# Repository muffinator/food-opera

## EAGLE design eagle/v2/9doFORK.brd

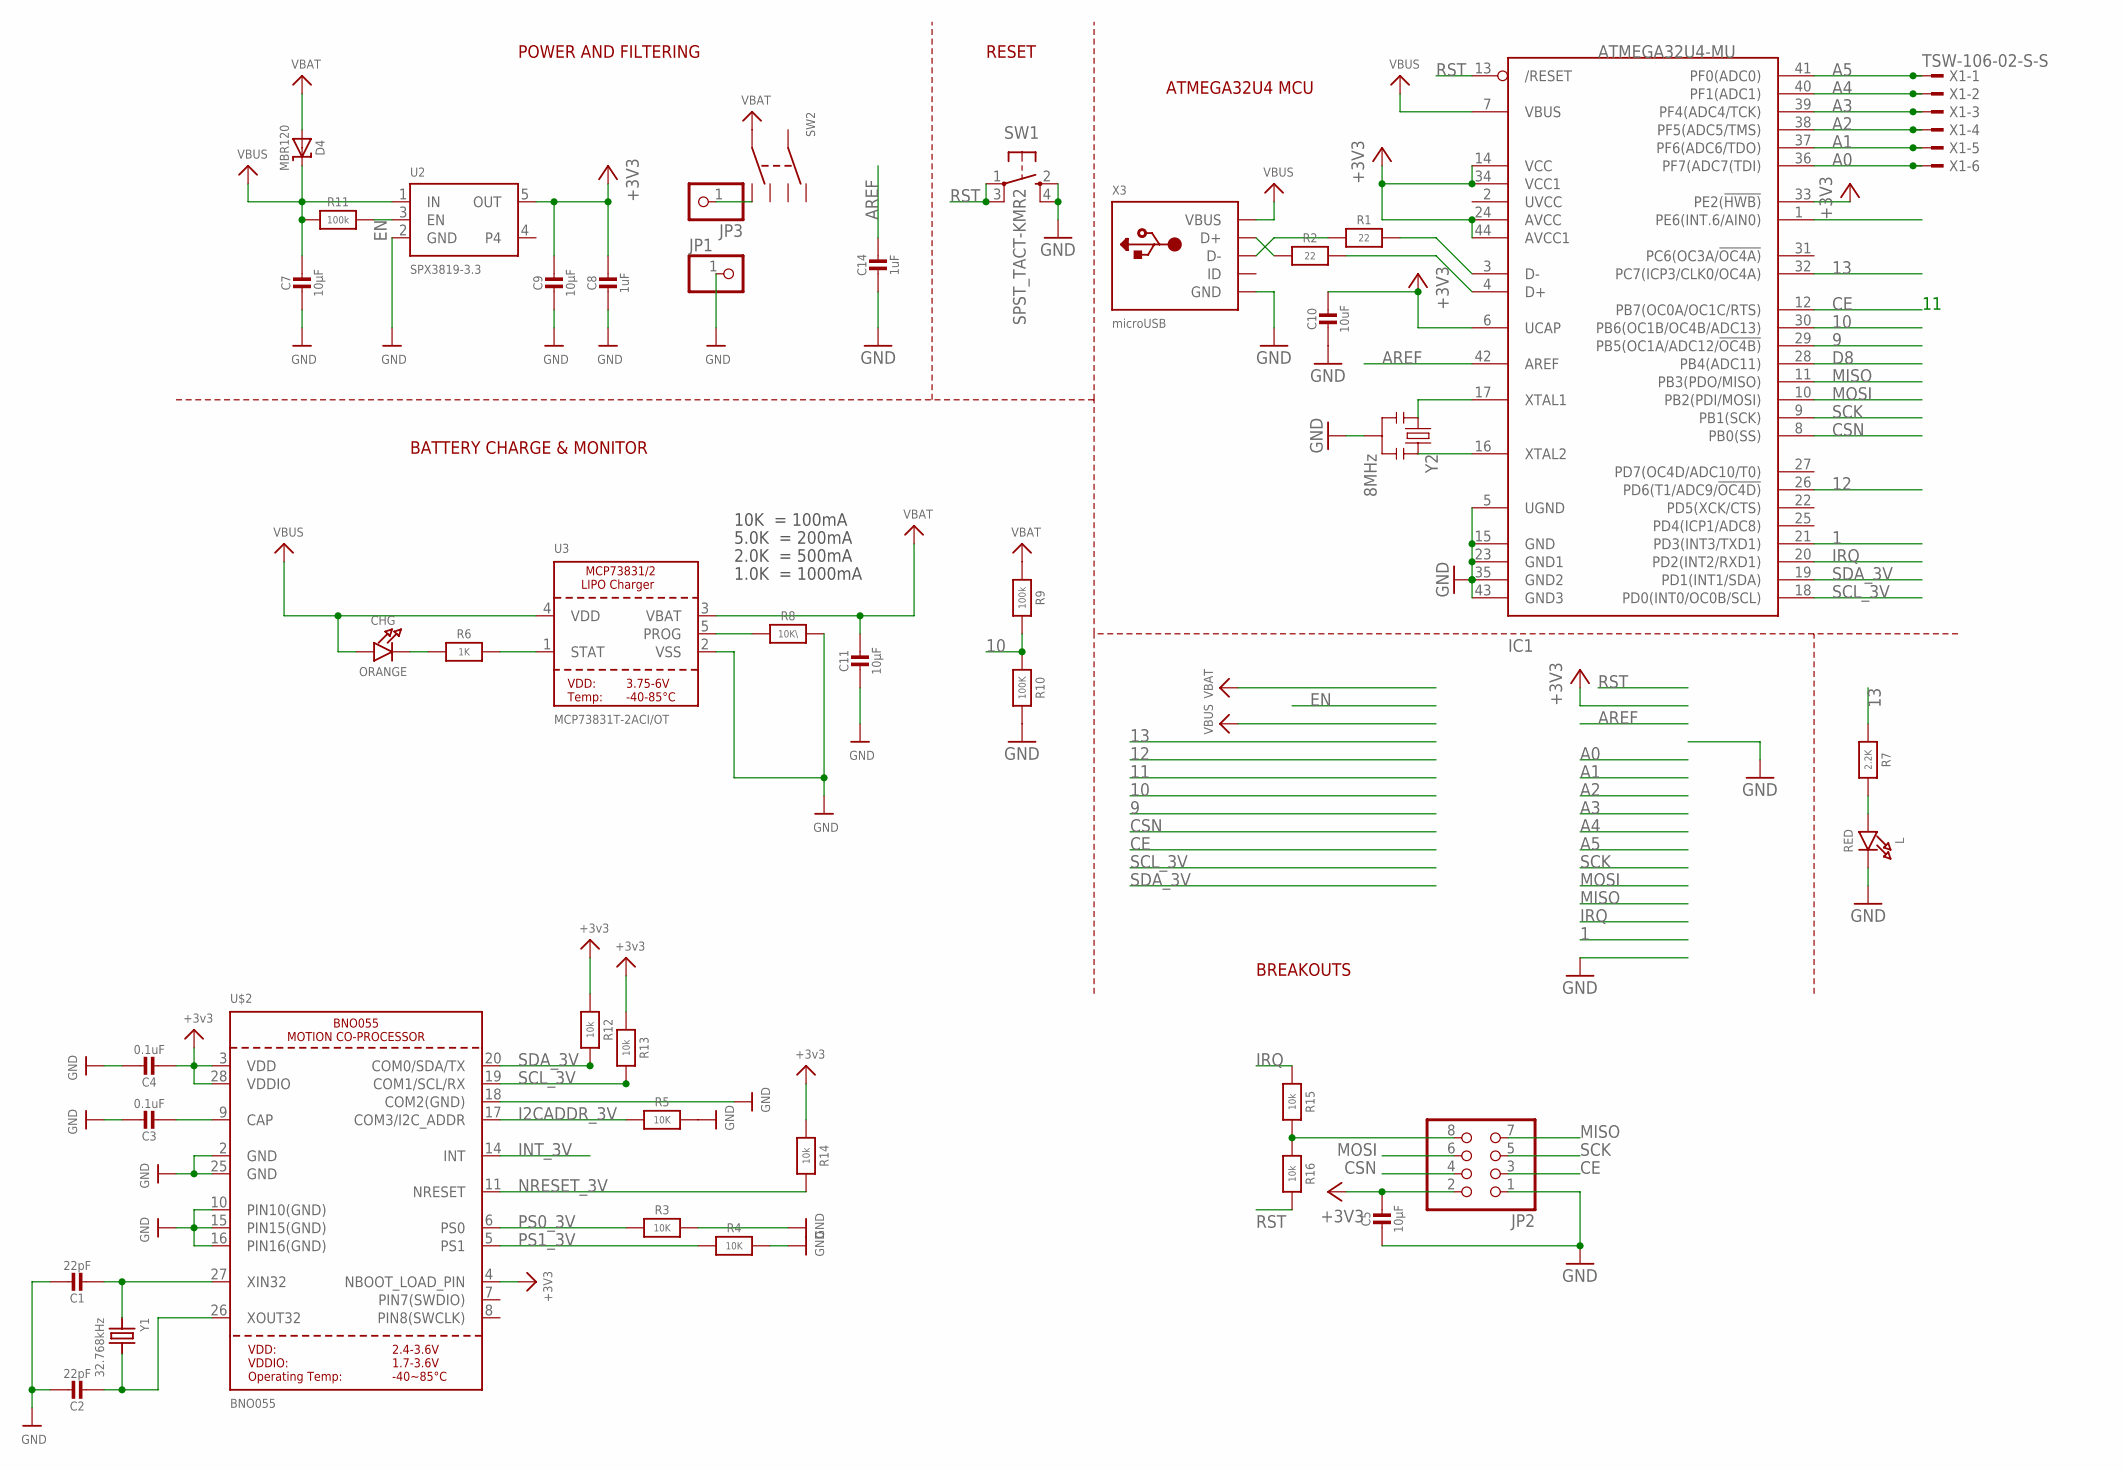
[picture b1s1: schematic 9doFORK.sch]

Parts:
C1, C2: 22pF; _0603
C3: 0.1uF; 0603-MINI
C4: 0.1uF; _0603
C5, C7, C9, C11: 10µF; 0805-NO
C8: 1uF; 0603-MINI
C10: 10uF; 0805-NO
C14: 1uF; 0603-NO
CHG: ORANGE; CHIPLED_0805_NOOUTLINE
D4: MBR120; SOD-123
IC1: ATMEGA32U4-MU; TQFN44_7MM
JP1, JP3: PINHD-1X1; 1X01
JP2: PINHD-2X4; 2X04
L: RED; CHIPLED_0805
R1, R2: 22; 0603-MINI
R3, R4, R5: 10K; 0603-MINI
R6: 1K; 0603-MINI
R7: 2.2K; 0603-MINI
R8: 10K\; 0603-MINI
R9, R11: 100k; 0603-MINI
R10: 100K; 0603-MINI
R12, R13, R14, R15, R16: 10k; 0603-MINI
SW1: SPST_TACT-KMR2; KMR2
SW2: SMT-SWITCH; JS202011JCQN
U2: SPX3819-3.3; SOT23-5
U3: MCP73831T-2ACI/OT; SOT23-5
U$2: BNO055
X1: TSW-106-02-S-S
X3: microUSB; 4UCONN_20329_V2
Y1: 32.768kHz; CRYSTAL_8X3.8
Y2: 8MHz; RESONATOR-SMD

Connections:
1: IC1.21 (PD3(INT3/TXD1))
9: IC1.29 (PB5(OC1A/ADC12/!OC4B))
10: IC1.30 (PB6(OC1B/OC4B/ADC13)), R9.2, R10.1
12: IC1.26 (PD6(T1/ADC9/!OC4D))
13: IC1.32 (PC7(ICP3/CLK0/OC4A)), R7.1
+3V3: C4.2, C5.1, C8.1, C9.1, C10.1, IC1.6 (UCAP), IC1.14 (VCC), IC1.24 (AVCC), IC1.33 (PE2(!HWB)), IC1.34 (VCC1), IC1.44 (AVCC1), JP2.2, R12.1, R13.1, R14.1, U2.5 (OUT), U$2.3 (VDD), U$2.4 (NBOOT_LOAD_PIN), U$2.28 (VDDIO)
A0: IC1.36 (PF7(ADC7(TDI)), X1.6
A1: IC1.37 (PF6(ADC6/TDO)), X1.5
A2: IC1.38 (PF5(ADC5/TMS)), X1.4
A3: IC1.39 (PF4(ADC4/TCK)), X1.3
A4: IC1.40 (PF1(ADC1)), X1.2
A5: IC1.41 (PF0(ADC0)), X1.1
AREF: C14.1, IC1.42 (AREF)
CE: IC1.12 (PB7(OC0A/OC1C/RTS)), JP2.3
CSN: IC1.8 (PB0(SS)), JP2.4
D8: IC1.28 (PB4(ADC11))
D+: IC1.4 (D+), R2.2
D-: IC1.3 (D-), R1.2
EN: R11.2, U2.3 (EN)
GND: C1.1, C2.1, C3.1, C4.1, C5.2, C7.2, C8.2, C9.2, C10.2, C11.2, C14.2, IC1.5 (UGND), IC1.15 (GND), IC1.23 (GND1), IC1.35 (GND2), IC1.43 (GND3), JP1.1, JP2.1, L.C, R3.2, R4.2, R5.2, R8.2, R10.2, SW1.2 (S), SW1.4 (S1), U2.2 (GND), U3.2 (VSS), U$2.2 (GND), U$2.10 (PIN10(GND)), U$2.15 (PIN15(GND)), U$2.16 (PIN16(GND)), U$2.18 (COM2(GND)), U$2.25 (GND), X3.BASE@1 (GND), X3.BASE@2 (GND), X3.GND, X3.SPRT@1 (GND), X3.SPRT@2 (GND), X3.SPRT@3 (GND), X3.SPRT@4 (GND), Y2.2
I2CADDR_3V: R5.1, U$2.17 (COM3/I2C_ADDR)
INT_3V: U$2.14 (INT)
IRQ: IC1.20 (PD2(INT2/RXD1)), R15.1
MISO: IC1.11 (PB3(PDO/MISO)), JP2.7
MOSI: IC1.10 (PB2(PDI/MOSI)), JP2.6
unnamed: C1.2, U$2.27 (XIN32), Y1.P$1 (1)
unnamed: C2.2, U$2.26 (XOUT32), Y1.P$4 (2)
unnamed: C3.2, U$2.9 (CAP)
unnamed: L.A, R7.2
unnamed: CHG.C, R6.1
unnamed: R6.2, U3.1 (STAT)
unnamed: R8.1, U3.5 (PROG)
unnamed: IC1.16 (XTAL2), Y2.3
unnamed: IC1.17 (XTAL1), Y2.1
unnamed: JP2.8, R15.2, R16.1
unnamed: JP3.1, SW2.1
unnamed: R2.1, X3.D+
unnamed: R1.1, X3.D-
NRESET_3V: R14.2, U$2.11 (NRESET)
PS0_3V: R3.1, U$2.6 (PS0)
PS1_3V: R4.1, U$2.5 (PS1)
RST: IC1.13 (/RESET), R16.2, SW1.1, SW1.3 (P1)
SCK: IC1.9 (PB1(SCK)), JP2.5
SCL_3V: IC1.18 (PD0(INT0/OC0B/SCL)), R13.2, U$2.19 (COM1/SCL/RX)
SDA_3V: IC1.19 (PD1(INT1/SDA)), R12.2, U$2.20 (COM0/SDA/TX)
VBAT: C11.1, D4.A, R9.1, SW2.2, U3.3 (VBAT)
VBUS: C7.1, CHG.A, D4.C, IC1.7 (VBUS), R11.1, U2.1 (IN), U3.4 (VDD), X3.VBUS

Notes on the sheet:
POWER AND FILTERING
RESET
ATMEGA32U4 MCU
10K = 100mA
5.0K = 200mA
2.0K = 500mA
1.0K = 1000mA
BATTERY CHARGE & MONITOR
BREAKOUTS

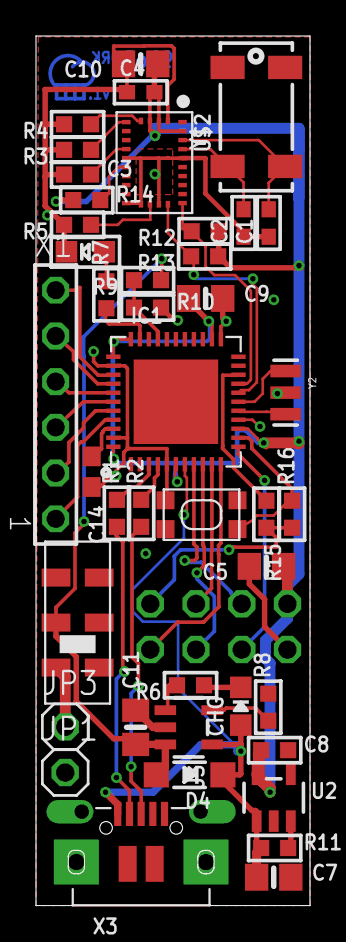
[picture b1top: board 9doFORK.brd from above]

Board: 2 copper layers, 15.2 x 48.3 mm, 43 parts (1 on the bottom side), 42 nets.

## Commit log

2017-06-08 adding arduino stuff
2017-06-08 added nrf.h to arduino sketches
2017-06-08 adding Max patch to parse data from accelerometer
2017-06-09 deleted: 9doFORK.b$1 deleted: 9doFORK.cmp deleted: 9doFORK.drd deleted: 9doFORK.dri deleted: 9doFORK.gpi deleted: 9doFORK.plc deleted: 9doFORK.pro deleted: 9doFORK.sol deleted: 9doFORK.stc deleted: 9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
2017-06-09 added gerber files for first board version
2017-06-11 commented the calibration data and added TX_DS wait
2017-06-15 Added v1 gerber files and BOM
2017-06-21 fixed some bugs in rawdata-rx, working on rev 2 for board, added expenses info
2017-06-22 finished rev2! - wish I added some more silkscreen art like a cool stylized fork or something... maybe a spaghetti poem!
2017-06-22 more gitignore
2017-07-02 adding new code to handle capacitive touch data and also enable muticiever mode - should have commited the capacitive touch data sketch first, but oh well!
2017-07-02 added capacitive touch sensor sending, gated sending BMO055 data depending on whether or not sensor is detected, and enabling multiciever mode
2017-07-02 added new structs to store data for each fork board attached
2017-07-02 fixed command prefix for setting rx and tx addresses
2017-07-02 added PIPE: prefix to serial out
2017-07-03 enable all datapipes
2017-07-03 added delta measurement for touch sensing and added some LED functionality (DRINKING and WAITER modes) using the FastLED library
2017-07-04 moved threshold definition
2017-07-05 replaced hardcoded 2 with CHANNEL so that the define will work
2017-07-05 now all LEDs in our light ring light up
2017-07-05 added some delays
2017-07-05 adding parsing for La Fura workshop
2017-07-05 a motor patch to test with
2017-07-05 this sound is required by the previous patch
2017-07-06 added max patch and sample audio for touching food sounds
2017-07-11 new nometoques automatically loads files
2017-07-12 2 ways to play Russian Roulette
2017-07-16 added expenses
2017-07-16 just an uncomment of the version line

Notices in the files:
parts and their libraries:
microbuilder: This work is placed in the public domain, and may be freely used for commercial and non-commercial work with the following conditions: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
SparkFun: Licensing: CC v3.0 Share-Alike You are welcome to use this library for commercial purposes.
